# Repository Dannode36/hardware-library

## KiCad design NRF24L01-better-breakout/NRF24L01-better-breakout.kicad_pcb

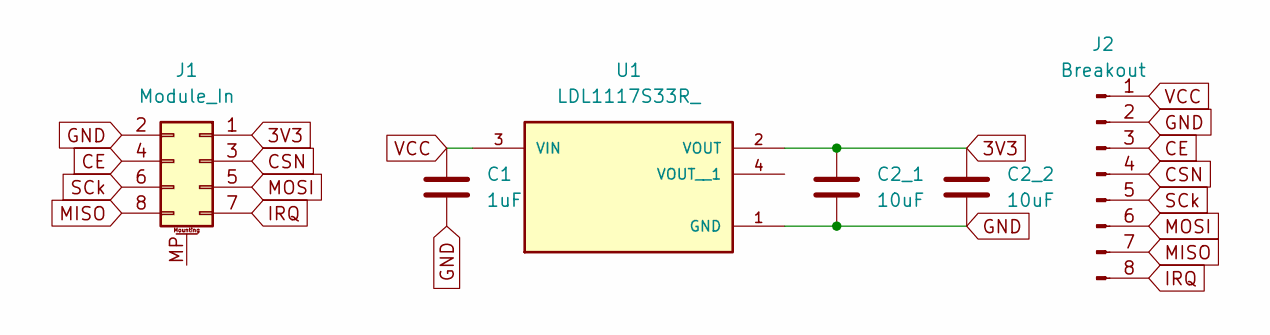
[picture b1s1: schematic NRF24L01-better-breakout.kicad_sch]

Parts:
C1: 1uF; C_1206_3216Metric_Pad1.33x1.80mm_HandSolder
C2_1: 10uF; CP_Radial_D5.0mm_P2.00mm
C2_2: 10uF; C_1206_3216Metric_Pad1.33x1.80mm_HandSolder
J1: Module_In; PinSocket_2x04_P2.54mm_Vertical
J2: Breakout; PinHeader_1x08_P2.54mm_Vertical
U1: LDL1117S33R_; LDL1117S50R_; PARTREV 7

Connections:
3V3: C2_1.1, C2_2.1, J1.1, U1.2 (VOUT)
CE: J1.4, J2.3
CSN: J1.3, J2.4
GND: C1.1, C2_1.2, C2_2.2, J1.2, J2.2, U1.1 (GND)
IRQ: J1.7, J2.8
MISO: J1.8, J2.7
MOSI: J1.5, J2.6
SCk: J1.6, J2.5
VCC: C1.2, J2.1, U1.3 (VIN)

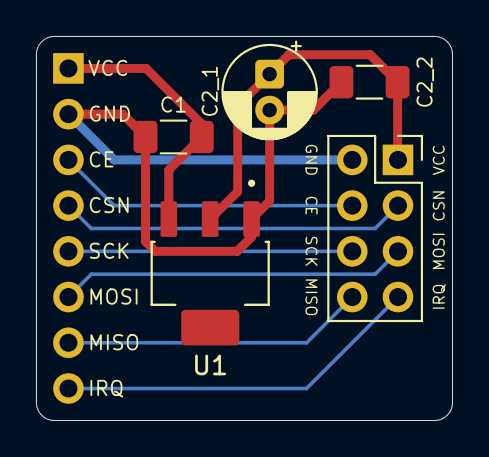
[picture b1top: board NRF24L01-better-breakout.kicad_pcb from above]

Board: 2 copper layers, 23.1 x 21.3 mm, 6 parts (1 on the bottom side), 9 nets.

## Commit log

2025-10-19 NRF24L01 Breakout
